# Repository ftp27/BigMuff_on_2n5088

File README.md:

Big Muff on 2n5088
=================
Clone of Big Muff Pi,  a fuzzbox produced in New York City by 
the Electro-Harmonix company, along with their Russian sister 
company Sovtek, primarily for use with the electric guitar. 
It is used by bassists as well due to the Big Muff's low end 
frequency response.

## Elements list

### Polyester film capacitors
* 0.01 uF 	- 1
* 0.1 uF	- 7
* 0.15 uF	- 1

### Ceramic capacitors
* 4.7 nF	- 1
* 470 pF	- 3

### Resistors
* 100 Ohm	- 3
* 820 Ohm	- 1
* 3.3 kOhm	- 1
* 7.5 kOhm	- 2
* 12 kOhm	- 4
* 33 kOhm	- 3
* 100 kOhm	- 4
* 390 kOhm	- 1
* 470 kOhm	- 3

### Linear potentiometers
* 100 kOhm	- 3

### Transistors
* 2n5008	- 4

### Diodes
* KT3102EM	- 4

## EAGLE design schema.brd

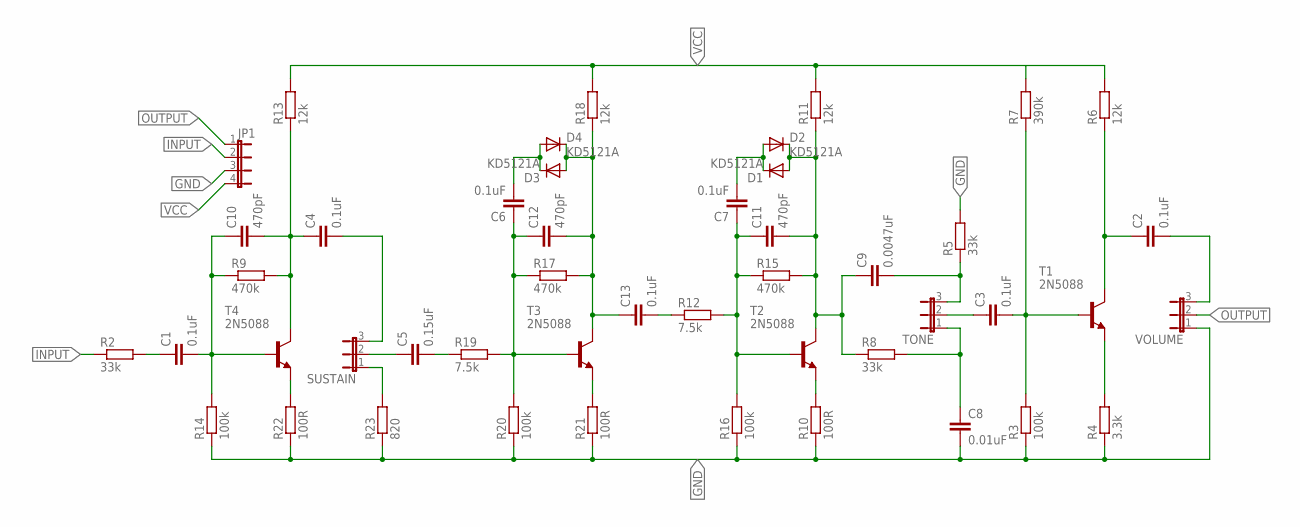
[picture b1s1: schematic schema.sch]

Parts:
C1, C2, C3, C4, C6, C7, C13: 0.1uF; C150-072X183
C5: 0.15uF; C150-054X183
C8: 0.01uF; C050-050X075
C9: 0.0047uF; C1206K
C10, C11, C12: 470pF; C0805K
D1, D2, D3, D4: KD5121A; DO35-10
JP1: JP4E; JP4
R2, R5, R8: 33k; R0805
R3, R14, R16, R20: 100k; R1206
R4: 3.3k; R1206
R6, R11, R13, R18: 12k; R1206
R7: 390k; R1206
R9, R15, R17: 470k; R1206
R10, R21, R22: 100R; R0805
R12, R19: 7.5k; R1206
R23: 820; R1206
SUSTAIN: JP2E; JP2
T1, T2, T3, T4: 2N5088; TO92
TONE: JP2E; JP2
VOLUME: JP2E; JP2

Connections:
GND: C8.2, JP1.3, R3.1, R4.1, R5.2, R10.1, R14.1, R16.1, R20.1, R21.1, R22.1, R23.1, VOLUME.1
INPUT: JP1.2, R2.1
unnamed: C1.2, C10.1, R9.1, R14.2, T4.2 (B)
unnamed: C1.1, R2.2
unnamed: C4.1, C10.2, R9.2, R13.1, T4.1 (C)
unnamed: R22.2, T4.3 (E)
unnamed: C3.2, R3.2, R7.1, T1.2 (B)
unnamed: C9.1, C11.2, D1.A, D2.C, R8.1, R11.1, R15.2, T2.1 (C)
unnamed: C4.2, SUSTAIN.3
unnamed: R23.2, SUSTAIN.1
unnamed: C5.1, SUSTAIN.2
unnamed: C2.1, R6.1, T1.1 (C)
unnamed: C5.2, R19.1
unnamed: C6.1, C12.1, R17.1, R19.2, R20.2, T3.2 (B)
unnamed: R21.2, T3.3 (E)
unnamed: R4.2, T1.3 (E)
unnamed: C7.2, D1.C, D2.A
unnamed: C2.2, VOLUME.3
unnamed: C8.1, R8.2, TONE.1
unnamed: C9.2, R5.1, TONE.3
unnamed: C3.1, TONE.2
unnamed: C13.2, R12.1
unnamed: C7.1, C11.1, R12.2, R15.1, R16.2, T2.2 (B)
unnamed: C6.2, D3.C, D4.A
unnamed: C12.2, C13.1, D3.A, D4.C, R17.2, R18.1, T3.1 (C)
unnamed: R10.2, T2.3 (E)
OUTPUT: JP1.1, VOLUME.2
VCC: JP1.4, R6.2, R7.2, R11.2, R13.2, R18.2

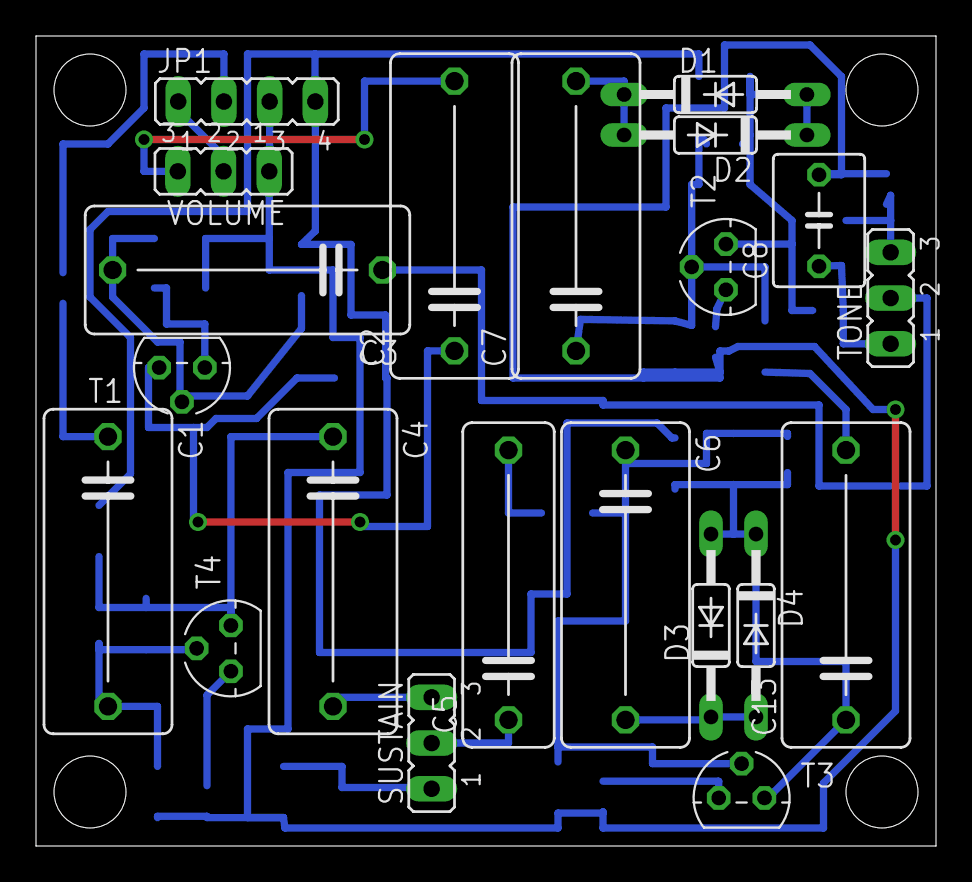
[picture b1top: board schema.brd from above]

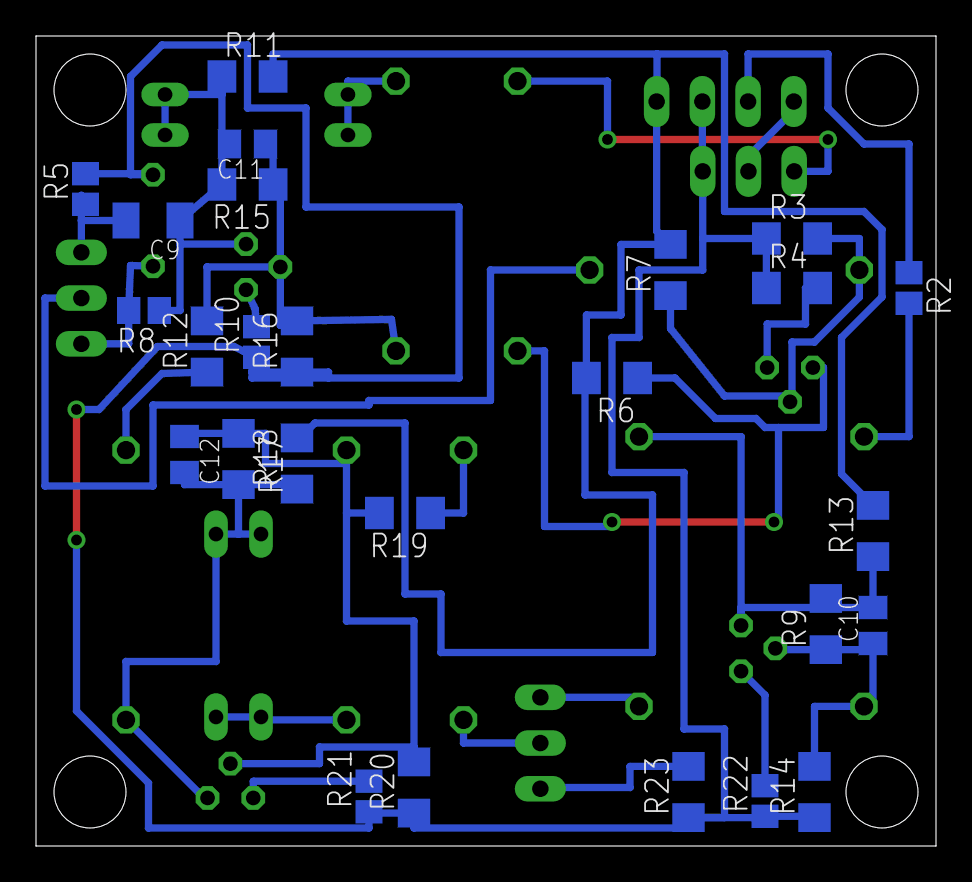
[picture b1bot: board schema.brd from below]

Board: 2 copper layers, 50.0 x 45.0 mm, 47 parts (26 on the bottom side), 28 nets.

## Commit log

2014-06-02 Add schematic and PCB
2014-06-02 Fixed README.md
2014-06-02 Add cover image
2014-06-04 Fix cover size
